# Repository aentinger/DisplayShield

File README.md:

💾 Display Shield
=================

# 📸 Image

# 📂 Description

The LXRobotics Display Shield facilitates the easy control of a Liquid Crystal Display's with 4 rows and 20 columns. The control of the display is done via I2C - only two Arduino Pins are required. The contrast of LCD can be adjusted using a rotary potentiometer. A 2-axis joystick with integrated pushbutton can be used as input device. For a quick and easy start, an open source Arduino library with sample programs is available.

**Features**

* Large LCD (Liquid Crystal Display) with 4 rows und 20 columns [4x20] 
* LCD-font color: white
* LCD-background color: blue
* LCD included in scope of delivery
* Background illumination on/off switchable
* Display contrast is adjustable via a rotary potentiometer
* Control over I2C - only two Arduino-Pins are required (SDA, SCL)
* I2C-PullUp-Resistors can be connected via jumpers
* 2-axis joystick with integrated pushbutton
* Display Shield firmware is open source
* Microcontroller programmed with current firmware is included in assembly kit
* Display Shield Firmwareupdate via Arduino possible
* Arduino Library with example programs is available on GitHub

# 🎥 [Video](images/display_shield_demo.mp4)

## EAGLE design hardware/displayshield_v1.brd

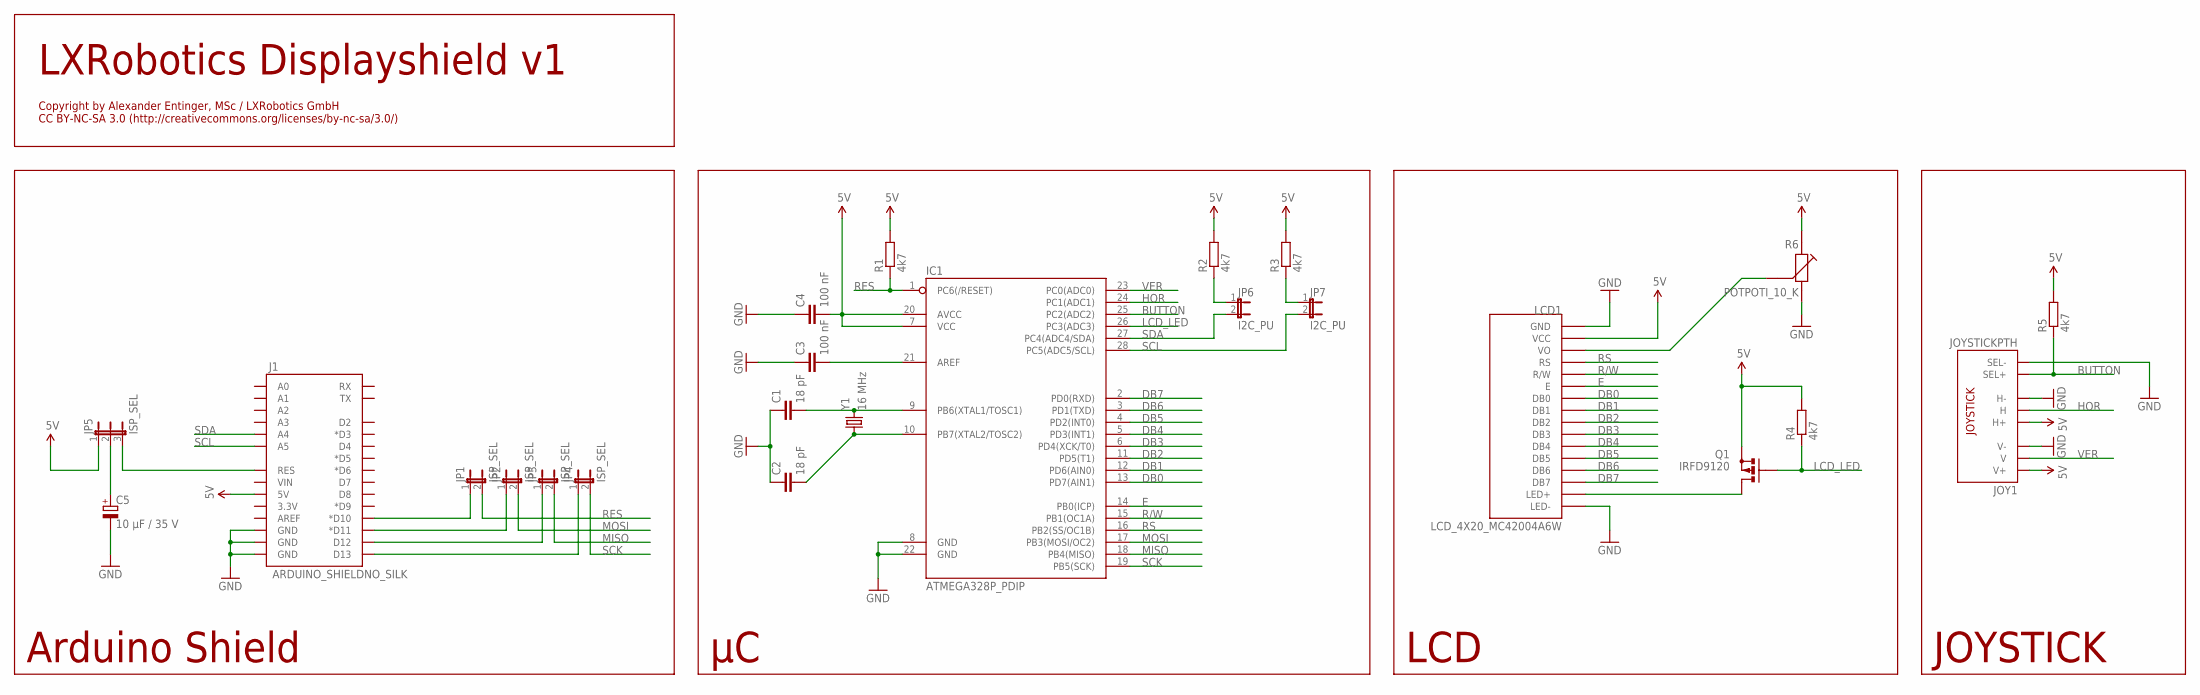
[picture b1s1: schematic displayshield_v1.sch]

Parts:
C1, C2: 18 pF; C025-025X050
C3, C4: 100 nF; C025-025X050
C5: 10 µF / 35 V; E2-5
IC1: ATMEGA328P_PDIP; DIL28-3
J1: ARDUINO_SHIELDNO_SILK; DUEMILANOVE_VIAS
JOY1: JOYSTICKPTH; JOYSTICK
JP1, JP2, JP3, JP4: ISP_SEL; JP1
JP5: ISP_SEL; JP2
JP6, JP7: I2C_PU; JP1
LCD1: LCD_4X20_MC42004A6W; LCD_3X40_MC42004A6W
Q1: IRFD9120; C370-01
R1, R2, R3, R4, R5: 4k7; 0204/5
R6: POTPOTI_10_K; POT_10K
Y1: 16 MHz; HC49US

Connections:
5V: C4.2, IC1.7 (VCC), IC1.20 (AVCC), J1.5V, JOY1.H1 (H+), JOY1.V1 (V+), JP5.1, LCD1.VCC, Q1.S, R1.2, R2.2, R3.2, R4.2, R5.2, R6.S
BUTTON: IC1.25 (PC2(ADC2)), JOY1.B1A (SEL+), R5.1
DB0: IC1.13 (PD7(AIN1)), LCD1.DB0
DB1: IC1.12 (PD6(AIN0)), LCD1.DB1
DB2: IC1.11 (PD5(T1)), LCD1.DB2
DB3: IC1.6 (PD4(XCK/T0)), LCD1.DB3
DB4: IC1.5 (PD3(INT1)), LCD1.DB4
DB5: IC1.4 (PD2(INT0)), LCD1.DB5
DB6: IC1.3 (PD1(TXD)), LCD1.DB6
DB7: IC1.2 (PD0(RXD)), LCD1.DB7
E: IC1.14 (PB0(ICP)), LCD1.E
GND: C1.1, C2.1, C3.1, C4.1, C5.-, IC1.8 (GND), IC1.22 (GND), J1.GND@0 (GND), J1.GND@1 (GND), J1.GND@2 (GND), JOY1.B2A (SEL-), JOY1.H3 (H-), JOY1.V3 (V-), LCD1.GND, LCD1.LED-, R6.E
HOR: IC1.24 (PC1(ADC1)), JOY1.H2 (H)
LCD_LED: IC1.26 (PC3(ADC3)), Q1.G, R4.1
MISO: IC1.18 (PB4(MISO)), JP3.2
MOSI: IC1.17 (PB3(MOSI/OC2)), JP2.2
unnamed: C2.2, IC1.10 (PB7(XTAL2/TOSC2)), Y1.1
unnamed: C1.2, IC1.9 (PB6(XTAL1/TOSC1)), Y1.2
unnamed: J1.D10 (*D10), JP1.1
unnamed: J1.D11 (*D11), JP2.1
unnamed: C3.2, IC1.21 (AREF)
unnamed: J1.D12, JP3.1
unnamed: J1.D13, JP4.1
unnamed: C5.+, JP5.2
unnamed: LCD1.LED+, Q1.D, Q1.D1 (D)
unnamed: LCD1.VO, R6.VAR
unnamed: J1.RES, JP5.3
unnamed: JP6.1, R2.1
unnamed: JP7.1, R3.1
R/W: IC1.15 (PB1(OC1A)), LCD1.R/W
RES: IC1.1 (PC6(/RESET)), JP1.2, R1.1
RS: IC1.16 (PB2(SS/OC1B)), LCD1.RS
SCK: IC1.19 (PB5(SCK)), JP4.2
SCL: IC1.28 (PC5(ADC5/SCL)), J1.A5, JP7.2
SDA: IC1.27 (PC4(ADC4/SDA)), J1.A4, JP6.2
VER: IC1.23 (PC0(ADC0)), JOY1.V2 (V)

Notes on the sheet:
Arduino Shield
LCD
JOYSTICK
Copyright by Alexander Entinger, MSc / LXRobotics GmbH CC BY-NC-SA 3.0 (http://creativecommons.org/licenses/by-nc-sa/3.0/)
LXRobotics Displayshield v1

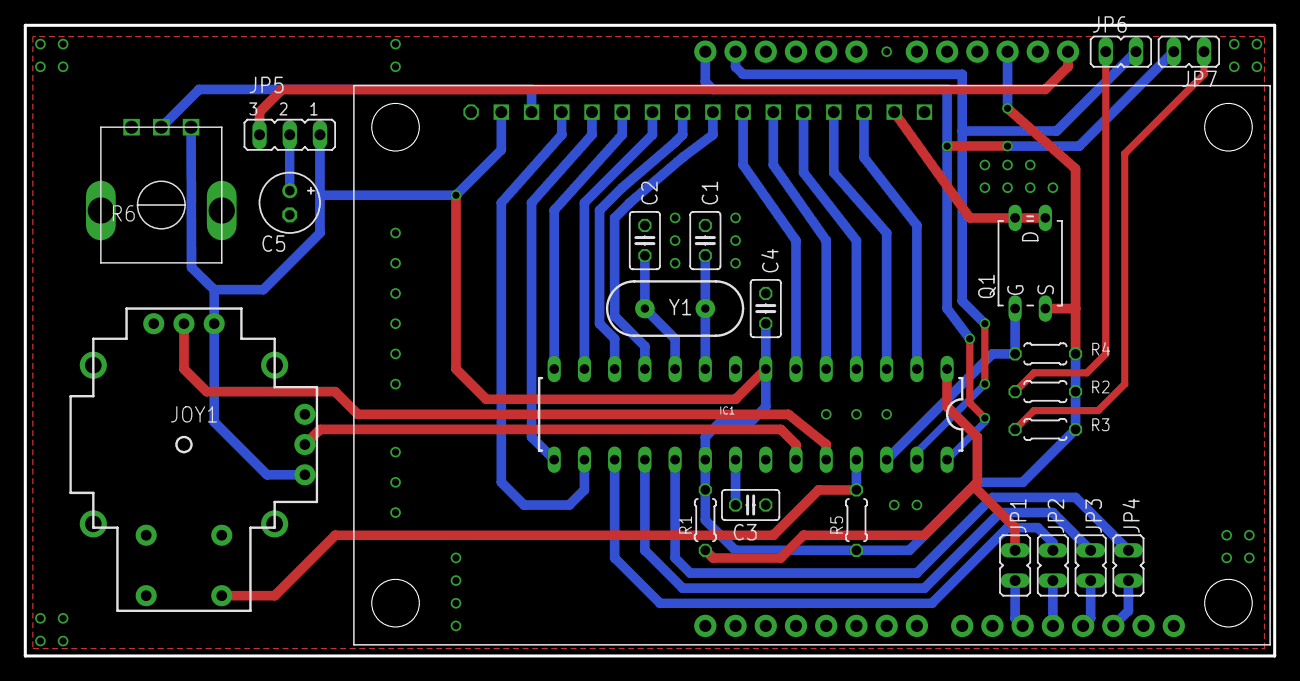
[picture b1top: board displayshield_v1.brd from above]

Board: 2 copper layers, 105.0 x 53.0 mm, 24 parts (0 on the bottom side), 36 nets.

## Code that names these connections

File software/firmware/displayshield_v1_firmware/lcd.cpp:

/**
 * @author Alexander Entinger, MSc / LXRobotics
 * @brief this module encapsulates the control of the lcd attached to the LXRobotics Display Shield
 * @file lcd.cpp
 * @license Attribution-NonCommercial-ShareAlike 3.0 Unported (CC BY-NC-SA 3.0) ( http://creativecommons.org/licenses/by-nc-sa/3.0/ )
 */

/* INCLUDE SECTION */

#include "lcd.h"
#include <LiquidCrystal.h>

/* DEFINE SECTION */

/* LCD BACKLIGHT */
// LCD_LED = PC3 = A3
#define LCD_LED_DDR     DDRC
#define LCD_LED_PORT    PORTC
#define LCD_LED         (1<<3)

/* CONSTANT SECTION */

/* LCD PROPERTIES */
// RS = PB2 = 10
static int const rs = 10;
// RW = PB1 = 9
static int const rw = 9;
// enable = PB0 = 8
static int const enable = 8;
// d0 = PD7 = 7
static int const d0 = 7;
static int const d1 = 6;
static int const d2 = 5;
static int const d3 = 4;
static int const d4 = 3;
static int const d5 = 2;
static int const d6 = 1;
// d7 = PD0 = 0
static int const d7 = 0;
// number of rows and cols of the lcd display
static int const LCD_COLS = 20;
static int const LCD_ROWS = 4;

/* GLOBAL VARIABLE SECTION */

LiquidCrystal my_lcd(rs,rw,enable,d0,d1,d2,d3,d4,d5,d6,d7);
static char display_content[LCD_ROWS][LCD_COLS];

/* CODE SECTION */

/**
 * @brief initializes the module
 */
void lcd::begin() {
  my_lcd.begin(LCD_COLS, LCD_ROWS);
  for(int r=0; r<LCD_ROWS; r++)
    for(int c=0; c<LCD_COLS; c++) display_content[r][c] = ' ';
  lcd::update();
  
  // set backlight to output and turn it off  
  LCD_LED_DDR |= LCD_LED;
  lcd::set_backlight(BACKLIGHT_OFF);
}

/**
 * @brief writes the content of line_content into the display buffer for row 'row'
 */
void lcd::print(unsigned int const row, char *line_content) {
  if(row > (LCD_ROWS-1)) return;
  int const length = strlen(line_content);
  for(int c=0; c<LCD_COLS; c++) {
    if(c < length)
      display_content[row][c] = line_content[c];
    else
      display_content[row][c] = ' ';
  }
}

/**
 * @brief writes any changes done by the write function onto the display
 */
void lcd::update() {
  for(int r=0; r<LCD_ROWS; r++) {
    my_lcd.setCursor(0,r);
    for(int c=0; c<LCD_COLS; c++) my_lcd.write(display_content[r][c]);
  }
}

/**
 * @brief control the lcd backlight
 */
void lcd::set_backlight(E_BACKLIGHT_STATUS const stat) {
  switch(stat) {
   case BACKLIGHT_ON: LCD_LED_PORT &= ~LCD_LED; break;
   case BACKLIGHT_OFF: LCD_LED_PORT |= LCD_LED; break;
   case BACKLIGHT_TOOGLE: LCD_LED_PORT ^= LCD_LED; break;
   default: break; 
  }
}

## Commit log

2014-06-13 initial checkin of lxr display shield software
2017-06-27 Adding hardware + images
2025-03-26 Add display shield demo video.
2025-03-26 Add BOM.
2025-03-26 Pretty up README.
2025-03-26 Use relative links.

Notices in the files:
README.md:
License: CC BY-NC-SA 4.0
parts and their libraries:
SparkFun-DigitalIC: Licensing: CC v3.0 Share-Alike You are welcome to use this library for commercial purposes.
